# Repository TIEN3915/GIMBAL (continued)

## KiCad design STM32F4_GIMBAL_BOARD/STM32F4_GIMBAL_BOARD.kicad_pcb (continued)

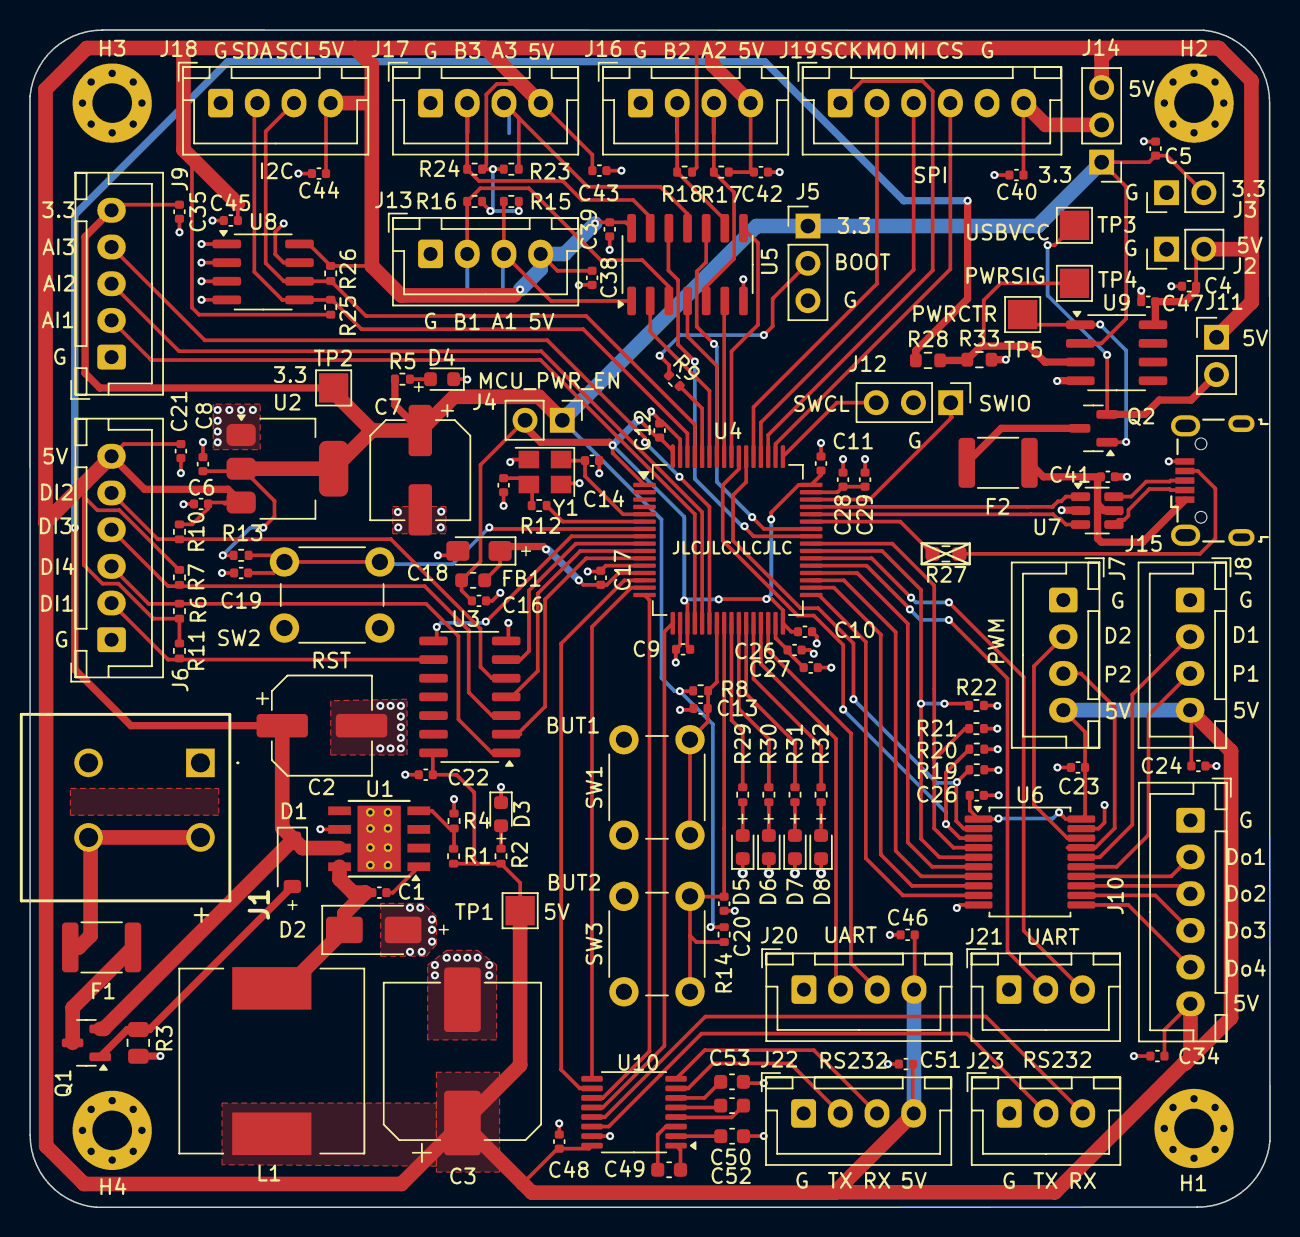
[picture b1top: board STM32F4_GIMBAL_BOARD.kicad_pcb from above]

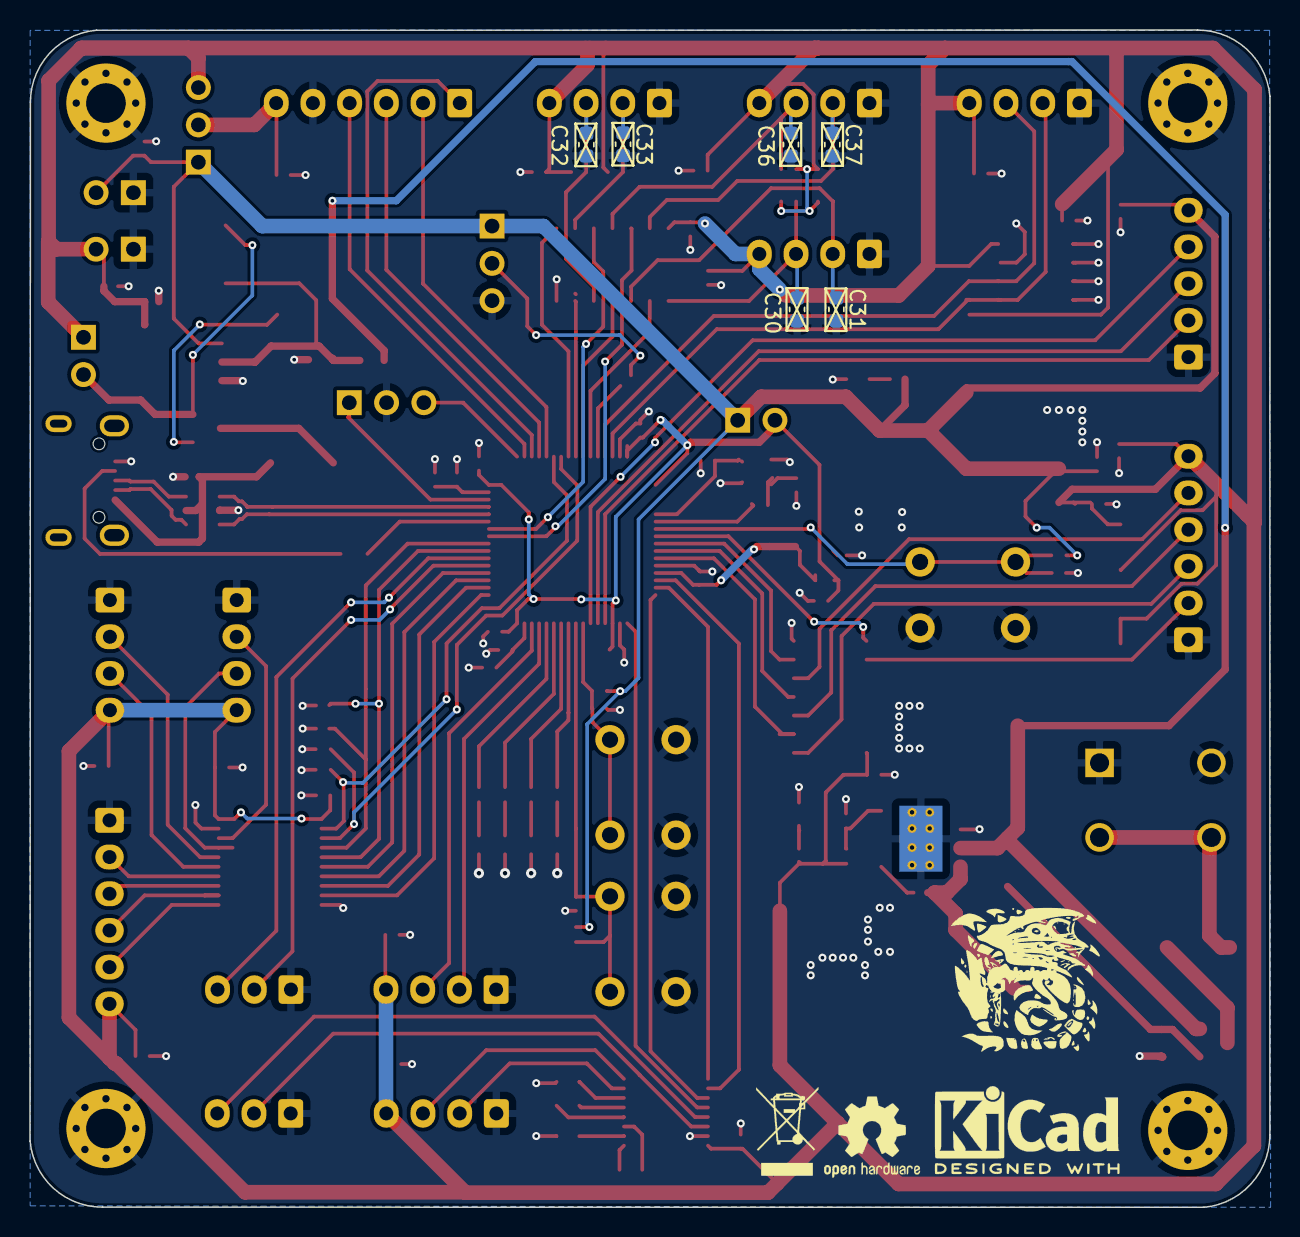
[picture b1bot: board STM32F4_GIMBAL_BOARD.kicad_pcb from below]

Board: 2 copper layers, 84.4 x 80.2 mm, 146 parts (6 on the bottom side), 109 nets.

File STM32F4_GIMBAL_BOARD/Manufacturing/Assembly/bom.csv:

Designator,Footprint,Quantity,Value,LCSC Part #
C1,402,1,10nF,C15195
"C10, C11, C12, C13, C16, C17, C19, C20, C21, C22, C23, C24, C25, C27, C29, C34, C35, C38, C39, C4, C40, C41, C42, C43, C44, C45, C46, C47, C48, C5, C51, C6, C8, C9",402,34,100nF,C1525
"C14, C15",402,2,10pF,C32949
C18,CP_EIA-3216-18_Kemet-A_Pad1.58x1.35mm_HandSolder,1,10uF Tantalum,C7171
"C2, C7",CP_Elec_6.3x7.7,2,RVT1E101M0607 100uF,C72477
"C26, C28",402,2,2.2uF,C12530
C3,CP_Elec_10x10.5,1,RVT1V471M1010 470uF,C3350
"C30, C31, C32, C33, C36, C37",603,6,? F,
"C49, C50, C52, C53",603,4,1uF 35V,C15849
D1,D_SOD-123,1,SOD123-5V,
D2,D_SMA,1,SS34,C8678
D3,603,1,LED_GREEN,
D4,603,1,LED_RED,
D5,603,1,YELLOW,
D6,603,1,BLUE,
D7,603,1,WHITE,
D8,603,1,ORGRANGE,
F1,1812,1,30V 200mA,
F2,1812,1,15V 500mA,
FB1,603,1,120?@100MHz,C1002
J1,KF142R5082P,1,24V DOMINO,
"J10, J19, J6",JST_XH_B6B-XH-A_1x06_P2.50mm_Vertical,3,Conn_01x06_Socket,
J11,PinHeader_1x02_P2.54mm_Vertical,1,Conn_01x02_Pin,
"J12, J14",PinHeader_1x03_P2.54mm_Vertical,2,Conn_01x03_Pin,
"J13, J16, J17, J18, J20, J22, J7, J8",JST_XH_B4B-XH-A_1x04_P2.50mm_Vertical,8,Conn_01x04_Socket,
J15,USB_Micro-B_Wuerth_629105150521,1,USB_B_Micro,
J2,PinHeader_1x02_P2.54mm_Vertical,1,5V_CONNECTOR,
"J21, J23",JST_XH_B3B-XH-A_1x03_P2.50mm_Vertical,2,Conn_01x03_Socket,
J3,PinHeader_1x02_P2.54mm_Vertical,1,3.3V_CONNECTOR,
J4,PinHeader_1x02_P2.54mm_Vertical,1,MCU_3.3_CONN,
J5,PinHeader_1x03_P2.54mm_Vertical,1,BOOT CONN,
J9,JST_XH_B5B-XH-A_1x05_P2.50mm_Vertical,1,Conn_01x05_Socket,
L1,L_12x12mm_H8mm,1,100uH,
"Q1, Q2",SOT-23,2,AO3401A,C15127
"R1, R10, R11, R13, R14, R15, R16, R17, R18, R23, R24, R6, R7, R8, R9",402,15,10K 0402,C25744
R12,402,1,100 0402,C25076
"R19, R20, R21, R22",402,4,10k,C25744
R2,402,1,1K 0402,C11702
"R25, R26",402,2,4.7K,C25900
R27,603,1,0 ohm 0603,
R28,603,1,10K 0603,C25804
"R29, R30, R31, R32",402,4,510,C25123
R3,805,1,4k7 0805,
R33,603,1,2.2K 0603,C4190
R4,402,1,3.3K 0402,C25890
R5,402,1,510 0402,C25123
SW1,SW_PUSH_6mm,1,BUTTON1,
SW2,SW_PUSH_6mm,1,RESET_SW,
SW3,SW_PUSH_6mm,1,BUTTON2,
TP1,TestPoint_Pad_2.0x2.0mm,1,5V TestPoint,
TP2,TestPoint_Pad_2.0x2.0mm,1,3.3V TestPoint,
TP3,TestPoint_Pad_2.0x2.0mm,1,USB PW TestPoint,
TP4,TestPoint_Pad_2.0x2.0mm,1,PWRSIG_TP,
TP5,TestPoint_Pad_2.0x2.0mm,1,PWRCTR_TP,
U1,TI_SO-PowerPAD-8_ThermalVias,1,TPS5430DDA,C9864
U10,TSSOP-16_4.4x5mm_P0.65mm,1,MAX3232IPW,C354121
U2,SOT-223-3_TabPin2,1,AMS1117S-3.3,C6186
"U3, U5",SOIC-14_3.9x8.7mm_P1.27mm,2,74HC14D,C5605
U4,LQFP-64_10x10mm_P0.5mm,1,STM32F405RGTx,C15742
U6,SSOP-20_5.3x7.2mm_P0.65mm,1,SN74HCT245DBR,C2676027
U7,SOT-23-6,1,USBLC6-2SC6,C5261088
U8,SOIC-8_3.9x4.9mm_P1.27mm,1,AT24C256C,
U9,SOIC-8_3.9x4.9mm_P1.27mm,1,LM358,C7950
Y1,Crystal_SMD_3225-4Pin_3.2x2.5mm,1,X322516MLB4SI-16MHz,C13738

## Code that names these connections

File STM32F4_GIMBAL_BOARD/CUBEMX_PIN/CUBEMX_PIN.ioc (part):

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Mcu.Name=STM32F405RGTx
Mcu.Package=LQFP64
Mcu.UserName=STM32F405RGTx
PA0-WKUP.Mode=Asynchronous
PA0-WKUP.Signal=UART4_TX
PA1.Mode=Asynchronous
PA1.Signal=UART4_RX
PA11.Mode=Host_Only
PA11.Signal=USB_OTG_FS_DM
PA12.Mode=Host_Only
PA12.Signal=USB_OTG_FS_DP
PA13.Signal=SYS_JTMS-SWDIO
PA14.Signal=SYS_JTCK-SWCLK
PA15.Mode=NSS_Signal_Hard_Output
PA15.Signal=SPI3_NSS
PA2.Mode=Asynchronous
PA2.Signal=USART2_TX
PA3.Mode=Asynchronous
PA3.Signal=USART2_RX
PA4.Signal=ADCx_IN4
PA5.Signal=ADCx_IN5
PA6.Signal=ADCx_IN6
PA7.GPIOParameters=GPIO_Label
PA7.GPIO_Label=GPIO_BUTTON1
PA7.Signal=GPIO_Input
PA8.GPIOParameters=GPIO_Label
PA8.GPIO_Label=TIM1_CH1_ENC3_B
PA8.Signal=S_TIM1_CH1
PA9.GPIOParameters=GPIO_Label
PA9.GPIO_Label=TIM1_CH2_ENC3_A
PA9.Signal=S_TIM1_CH2
PB0.GPIOParameters=GPIO_Label
PB0.GPIO_Label=GPIO_LED2
PB0.Signal=GPIO_Output
PB1.GPIOParameters=GPIO_Label
PB1.GPIO_Label=GPIO_LED3
PB1.Signal=GPIO_Output
PB10.Mode=Asynchronous
PB10.Signal=USART3_TX
PB11.Mode=Asynchronous
PB11.Signal=USART3_RX
PB12.GPIOParameters=GPIO_Label
PB12.GPIO_Label=GPIO_DO1
PB12.Signal=GPIO_Output
PB13.GPIOParameters=GPIO_Label
PB13.GPIO_Label=GPIO_DO2
PB13.Signal=GPIO_Output
PB14.GPIOParameters=GPIO_Label
PB14.GPIO_Label=GPIO_DO3
PB14.Signal=GPIO_Output
PB15.GPIOParameters=GPIO_Label
PB15.GPIO_Label=GPIO_DO4
PB15.Signal=GPIO_Output
PB2.GPIOParameters=GPIO_Label
PB2.GPIO_Label=GPIO_LED4
PB2.Signal=GPIO_Output
PB3.GPIOParameters=GPIO_Label
PB3.GPIO_Label=TIM2_CHANNEL2_PWM2
PB3.Signal=S_TIM2_CH2
PB4.GPIOParameters=GPIO_Label
PB4.GPIO_Label=TIM3_CH1_ENC2_B
PB4.Signal=S_TIM3_CH1
PB5.GPIOParameters=GPIO_Label
PB5.GPIO_Label=TIM3_CH2_ENC2_A
PB5.Signal=S_TIM3_CH2
PB6.GPIOParameters=GPIO_Label
PB6.GPIO_Label=TIM4_CH1_ENC1_B
PB6.Signal=S_TIM4_CH1
PB7.GPIOParameters=GPIO_Label
PB7.GPIO_Label=TIM4_CH2_ENC1_A
PB7.Signal=S_TIM4_CH2
PB8.Mode=I2C
PB8.Signal=I2C1_SCL
PB9.Mode=I2C
PB9.Signal=I2C1_SDA
PC0.Signal=GPXTI0
PC1.Signal=GPXTI1
PC10.Mode=Full_Duplex_Master
PC10.Signal=SPI3_SCK
PC11.Mode=Full_Duplex_Master
PC11.Signal=SPI3_MISO
PC12.Mode=Full_Duplex_Master
PC12.Signal=SPI3_MOSI
PC2.Signal=GPXTI2
PC3.Signal=GPXTI3
PC4.GPIOParameters=GPIO_Label
PC4.GPIO_Label=GPIO_BUTTON2
PC4.Signal=GPIO_Input
PC5.GPIOParameters=GPIO_Label
PC5.GPIO_Label=GPIO_LED1
PC5.Signal=GPIO_Output
PC6.Mode=Asynchronous
PC6.Signal=USART6_TX
PC7.Mode=Asynchronous
PC7.Signal=USART6_RX
PC8.GPIOParameters=GPIO_Label
PC8.GPIO_Label=TIM8_CHANNEL3_PWM1
PC8.Signal=S_TIM8_CH3
PC9.GPIOParameters=GPIO_Label
PC9.GPIO_Label=GPIO_DIR1
PC9.Signal=GPIO_Output
PD2.GPIOParameters=GPIO_Label
PD2.GPIO_Label=GPIO_DIR2
PD2.Signal=GPIO_Output
PH0-OSC_IN.Mode=HSE-External-Oscillator
PH0-OSC_IN.Signal=RCC_OSC_IN
PH1-OSC_OUT.Mode=HSE-External-Oscillator
PH1-OSC_OUT.Signal=RCC_OSC_OUT
RCC.HSE_VALUE=25000000
RCC.SYSCLKFreq_VALUE=16000000
board=custom

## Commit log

2024-12-04 GIMBAL_BOARD RELEASE
